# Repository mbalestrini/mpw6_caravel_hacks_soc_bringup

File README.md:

# mpw6_caravel_hacks_soc_bringup

## **MPW6 silicon test: Hack SoC project inside Caravel architecture**

---
### **Architecture overview:**

### **MPRJ_IO Connections:**

| |  | |  
|---|---|---|
|RAM_CS_N |output|MPRJ_IO[8]
|RAM_CSK |output|MPRJ_IO[9]
|RAM_SIO0 |inout|MPRJ_IO[10]
|RAM_SIO1 |inout|MPRJ_IO[11]
|RAM_SIO2 |inout|MPRJ_IO[12]
|RAM_SIO3 |inout|MPRJ_IO[13]
||||
|ROM_CS_N |output|MPRJ_IO[14]
|ROM_CSK |output|MPRJ_IO[15]
|ROM_SIO0 |inout|MPRJ_IO[16]
|ROM_SIO1 |inout|MPRJ_IO[17]
|ROM_SIO2 |inout|MPRJ_IO[18]
|ROM_SIO3 |inout|MPRJ_IO[19]
||||
|VRAM_CS_N |output|MPRJ_IO[20]
|VRAM_CSK |output|MPRJ_IO[21]
|VRAM_SIO0 |inout|MPRJ_IO[22]
|VRAM_SIO1 |inout|MPRJ_IO[23]
|VRAM_SIO2 |inout|MPRJ_IO[24]
|VRAM_SIO3 |inout|MPRJ_IO[25]
||||
|HACK_EXTERNAL_RESET|input|MPRJ_IO[26]
||||
|DISPLAY_VSYNC |output|MPRJ_IO[27]
|DISPLAY_HSYNC |output|MPRJ_IO[28]
|DISPLAY_RGB |output|MPRJ_IO[29]
||||
|GPIO_I_0|input|MPRJ_IO[30]
|GPIO_I_1|input|MPRJ_IO[31]
|GPIO_I_2|input|MPRJ_IO[32]
|GPIO_I_3|input|MPRJ_IO[33]
||||
|GPIO_O_0|output|MPRJ_IO[34]
|GPIO_O_1|output|MPRJ_IO[35]
|GPIO_O_2|output|MPRJ_IO[36]
|GPIO_O_3|output|MPRJ_IO[37]

---

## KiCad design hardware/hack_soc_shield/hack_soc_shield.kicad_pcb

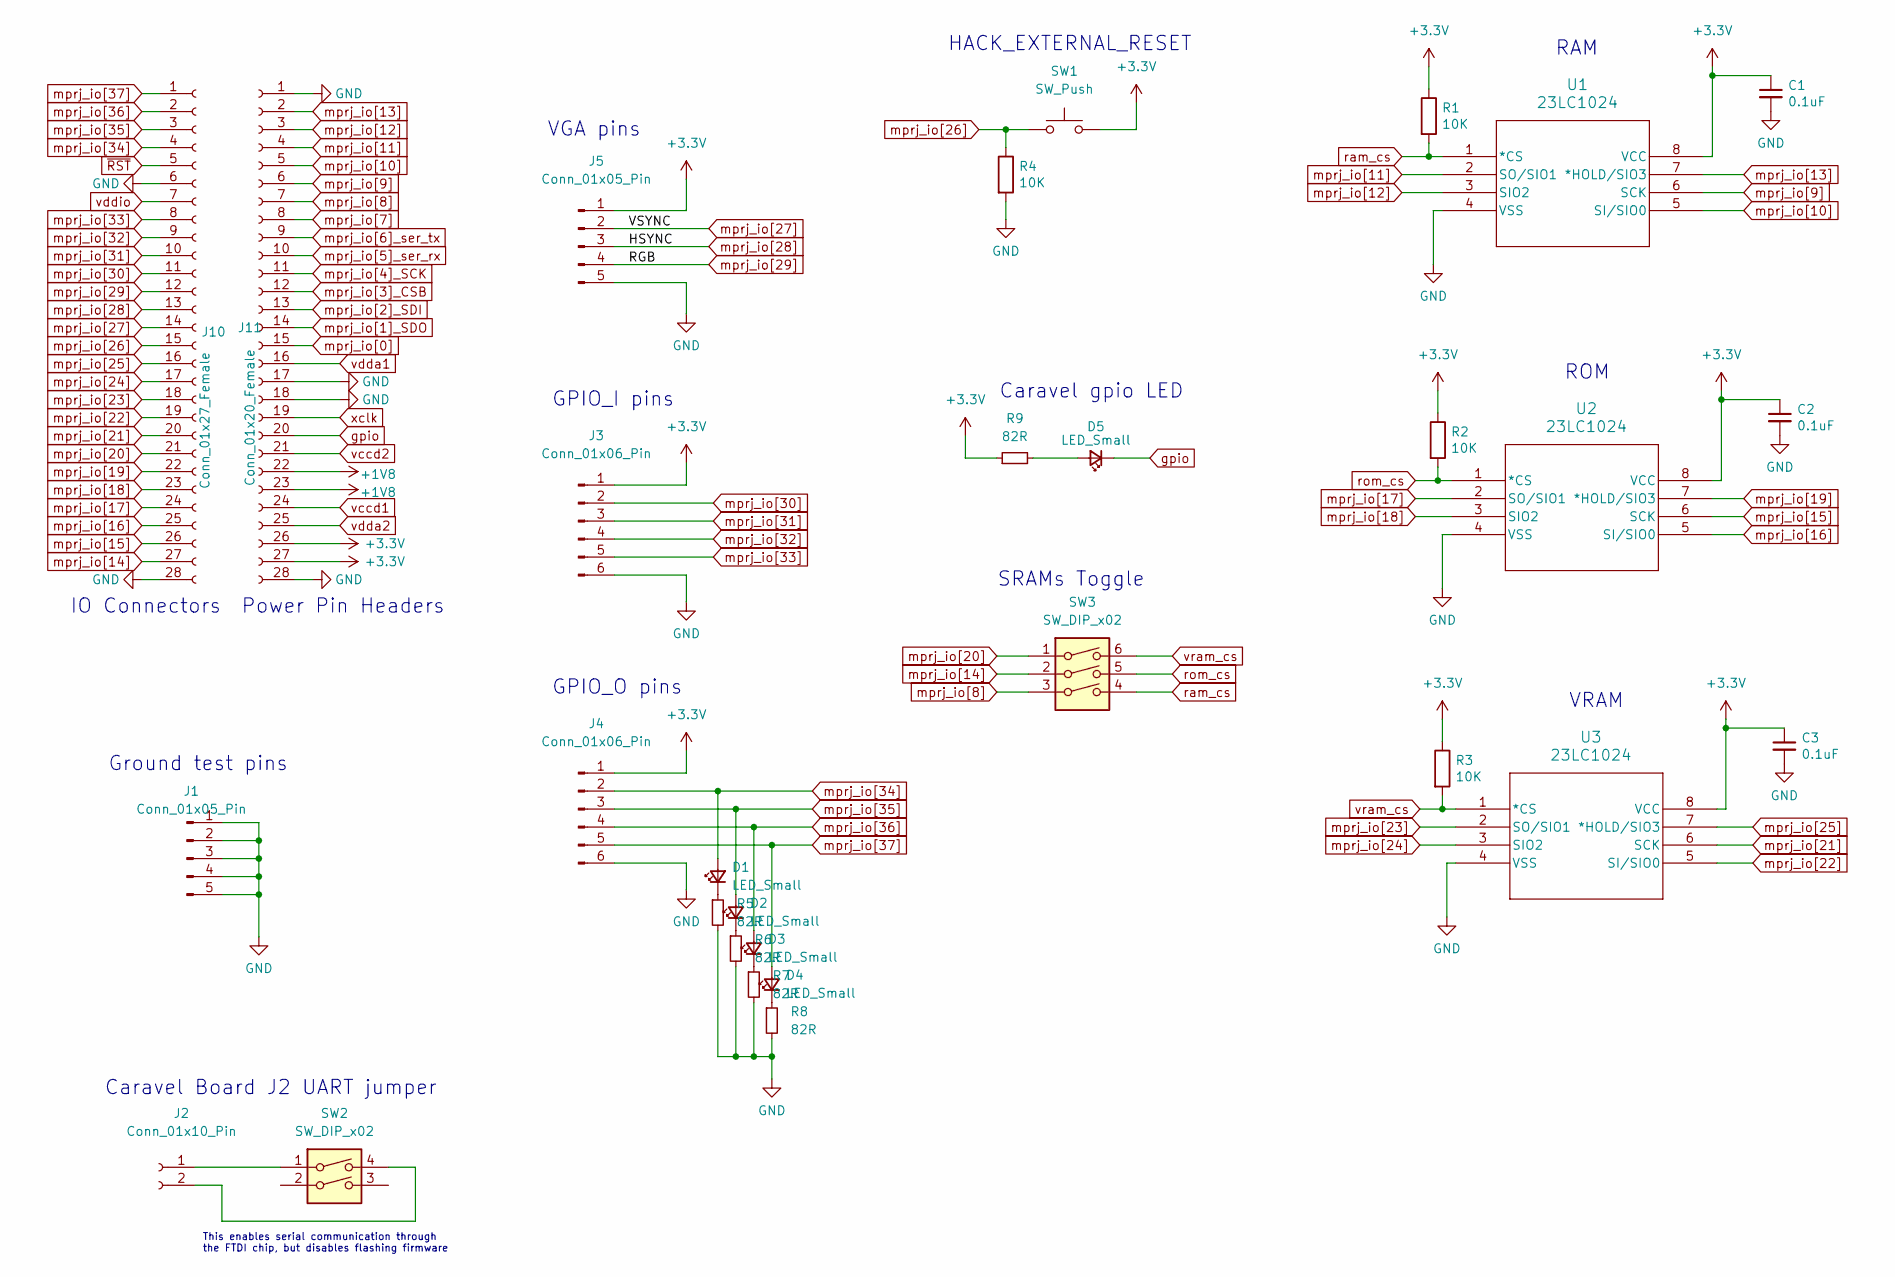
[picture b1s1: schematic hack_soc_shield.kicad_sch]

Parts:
C1, C2, C3: 0.1uF; C_Disc_D6.0mm_W2.5mm_P5.00mm
D1, D2, D3, D4, D5: LED_Small; LED_1206_3216Metric_Pad1.42x1.75mm_HandSolder
J1, J5: Conn_01x05_Pin; PinHeader_1x05_P2.54mm_Vertical
J2: Conn_01x10_Pin; PinHeader_1x02_P2.54mm_Vertical
J3, J4: Conn_01x06_Pin; PinHeader_1x06_P2.54mm_Vertical
J10: Conn_01x27_Female; PinHeader_1x28_P2.54mm_Vertical
J11: Conn_01x20_Female; PinHeader_1x28_P2.54mm_Vertical
R1, R2, R3, R4: 10K; R_Axial_DIN0204_L3.6mm_D1.6mm_P5.08mm_Horizontal
R5, R6, R7, R8, R9: 82R; R_1206_3216Metric_Pad1.30x1.75mm_HandSolder
SW1: SW_Push; SW_PUSH_6mm
SW2: SW_DIP_x02; SW_DIP_SPSTx02_Slide_9.78x7.26mm_W7.62mm_P2.54mm
SW3: SW_DIP_x02; SW_DIP_SPSTx03_Slide_9.78x9.8mm_W7.62mm_P2.54mm
U1, U2, U3: 23LC1024; SOIC8-N_MC_MCH

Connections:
+1V8: J11.22, J11.23
+3.3V: C1.1, C2.1, C3.1, J3.1, J4.1, J5.1, J11.26, J11.27, R1.1, R2.1, R3.1, R9.1, SW1.2, U1.8 (VCC), U2.8 (VCC), U3.8 (VCC)
GND: C1.2, C2.2, C3.2, J1.1, J1.2, J1.3, J1.4, J1.5, J5.5, J10.6, J10.28, J11.1, J11.17, J11.18, J11.28, R4.2, R5.2, R6.2, R7.2, R8.2, U1.4 (VSS), U2.4 (VSS), U3.4 (VSS)
unnamed: D1.1 (K), R5.1
unnamed: D2.1 (K), R6.1
unnamed: D3.1 (K), R7.1
unnamed: D4.1 (K), R8.1
unnamed: D5.2 (A), R9.2
unnamed: J2.1, SW2.1
unnamed: J2.2, SW2.4
gpio: D5.1 (K), J11.20
mprj_io[0]: J11.15
mprj_io[1]_SDO: J11.14
mprj_io[2]_SDI: J11.13
mprj_io[3]_CSB: J11.12
mprj_io[4]_SCK: J11.11
mprj_io[5]_ser_rx: J11.10
mprj_io[6]_ser_tx: J11.9
mprj_io[7]: J11.8
mprj_io[8]: J11.7, SW3.3
mprj_io[9]: J11.6, U1.6 (SCK)
mprj_io[10]: J11.5, U1.5 (SI/SIO0)
mprj_io[11]: J11.4, U1.2 (SO/SIO1)
mprj_io[12]: J11.3, U1.3 (SIO2)
mprj_io[13]: J11.2, U1.7 (*HOLD/SIO3)
mprj_io[14]: J10.27, SW3.2
mprj_io[15]: J10.26, U2.6 (SCK)
mprj_io[16]: J10.25, U2.5 (SI/SIO0)
mprj_io[17]: J10.24, U2.2 (SO/SIO1)
mprj_io[18]: J10.23, U2.3 (SIO2)
mprj_io[19]: J10.22, U2.7 (*HOLD/SIO3)
mprj_io[20]: J10.21, SW3.1
mprj_io[21]: J10.20, U3.6 (SCK)
mprj_io[22]: J10.19, U3.5 (SI/SIO0)
mprj_io[23]: J10.18, U3.2 (SO/SIO1)
mprj_io[24]: J10.17, U3.3 (SIO2)
mprj_io[25]: J10.16, U3.7 (*HOLD/SIO3)
mprj_io[26]: J10.15, R4.1, SW1.1
mprj_io[27]: J5.2, J10.14
mprj_io[28]: J5.3, J10.13
mprj_io[29]: J5.4, J10.12
mprj_io[30]: J3.2, J10.11
mprj_io[31]: J3.3, J10.10
mprj_io[32]: J3.4, J10.9
mprj_io[33]: J3.5, J10.8
mprj_io[34]: D1.2 (A), J4.2, J10.4
mprj_io[35]: D2.2 (A), J4.3, J10.3
mprj_io[36]: D3.2 (A), J4.4, J10.2
mprj_io[37]: D4.2 (A), J4.5, J10.1
ram_cs: R1.2, SW3.4, U1.1 (*CS)
rom_cs: R2.2, SW3.5, U2.1 (*CS)
vccd1: J11.24
vccd2: J11.21
vdda1: J11.16
vdda2: J11.25
vddio: J10.7
vram_cs: R3.2, SW3.6, U3.1 (*CS)
xclk: J11.19
~RST: J10.5

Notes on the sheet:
SRAMs Toggle
ROM
IO Connectors
Caravel gpio LED
Power Pin Headers
Caravel Board J2 UART jumper
Ground test pins
This enables serial communication through the FTDI chip, but disables flashing firmware
GPIO_I pins
VRAM
VGA pins
RAM
HACK_EXTERNAL_RESET
GPIO_O pins

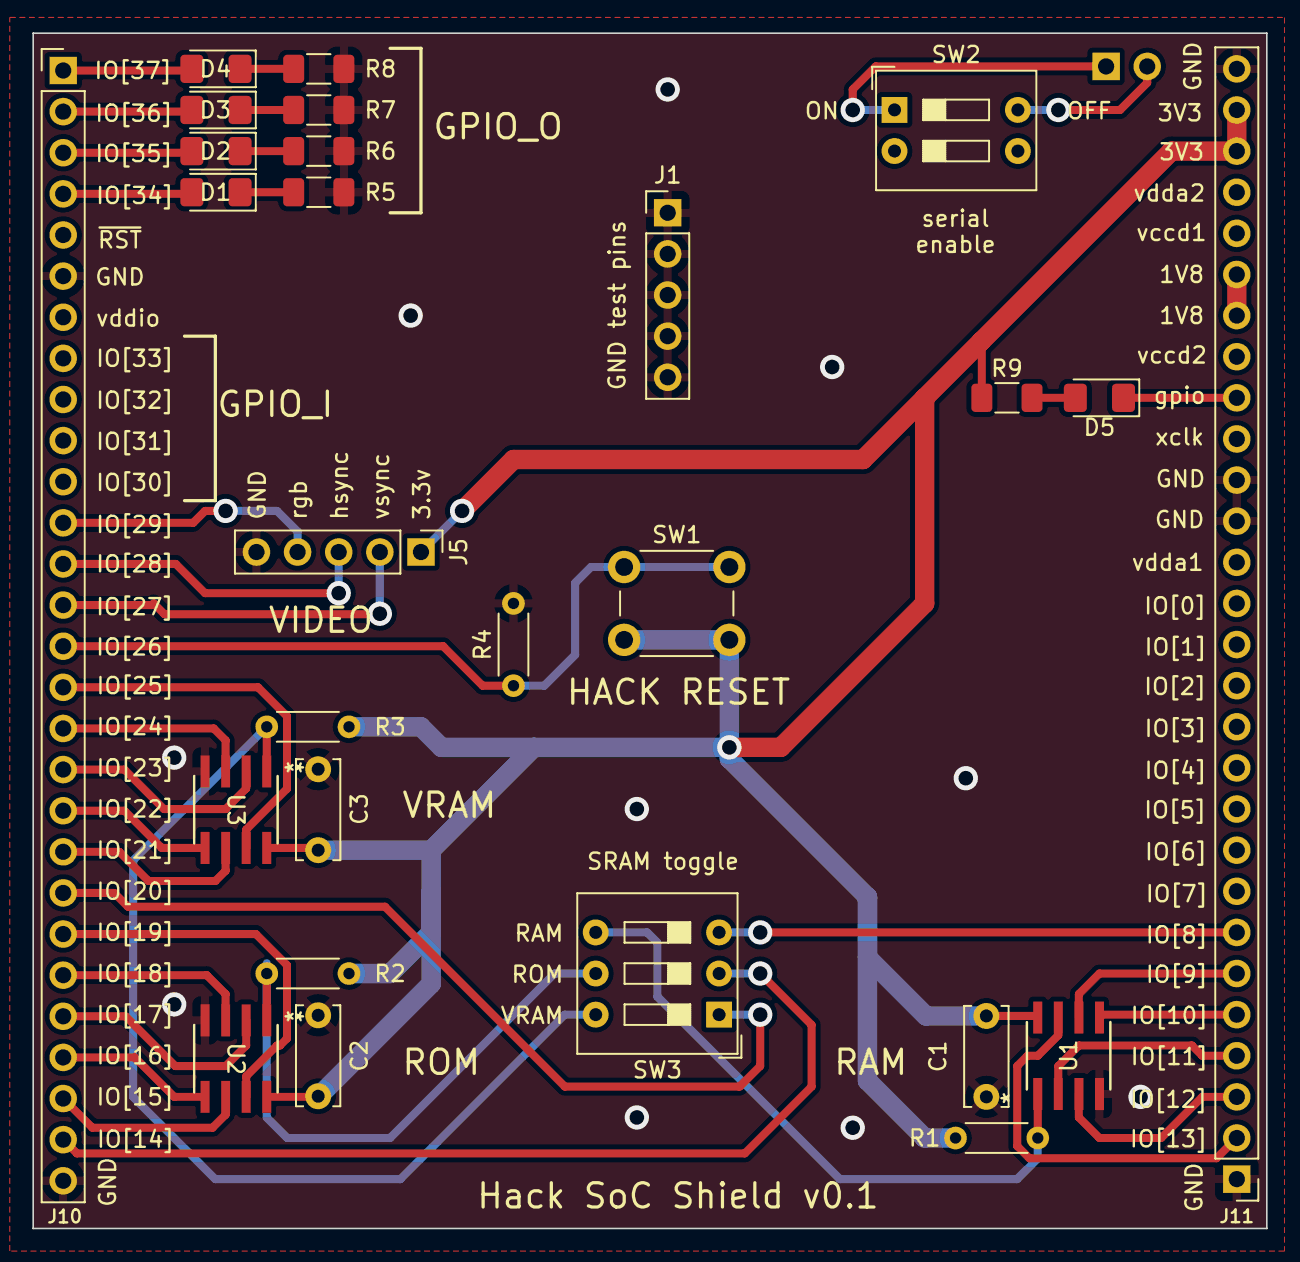
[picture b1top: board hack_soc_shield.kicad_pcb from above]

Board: 2 copper layers, 76.2 x 73.8 mm, 28 parts (1 on the bottom side), 40 nets.

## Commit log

2024-01-26 Add .gitignore file
2024-01-26 Add hardware folder
2024-01-26 Update hack_soc_shield
2024-01-26 Update hardware
2024-01-30 Update hardware and hack tests
2024-02-07 Add libgcc to makefiles
